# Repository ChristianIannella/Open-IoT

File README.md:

# Open IoT

Open IoT è un progetto open-source e open-hardware che ha lo scopo di offrire soluzioni IoT ai Maker e non solo.
Tutti i dispositivi Open IoT sono pronti per essere collegati all' impianto domestico, [qui](https://github.com/ChristianIannella/Open-IoT/tree/main) potete trovare schemi, gerber file ed esempi.

I dispositivi sono basati su ESP8266 e ESP32 questo permette connettività WiFi e [ESPNOW](https://www.espressif.com/en/solutions/low-power-solutions/esp-now), un protocollo proprietario ESPRESSIF. 

Le schede possono essere programmate sia da ambiente [Arduino](https://www.arduino.cc/en/software) sia [PlatformIO](https://platformio.org/) 

Su ogni dispositivo è presente un connettore FFC a 6 poli grazie al quale è possibile collegare il [programmatore](https://github.com/ChristianIannella/Open-IoT/tree/main/ESP%20Uploader) per cambiare firmware o testare il dispositivo.

# ELENCO DISPOSITIVI

- [ESP Uploader](https://github.com/ChristianIannella/Open-IoT/tree/main/ESP%20Uploader)
- [ESP8266 Relay](https://github.com/ChristianIannella/Open-IoT/tree/main/Relay)
- [ESP8266 Encoder](https://github.com/ChristianIannella/Open-IoT/tree/main/Encoder)
- [ESP8266 Thermometer](https://github.com/ChristianIannella/Open-IoT/tree/main/Thermometer)
- [ESP8266 Led Driver](https://github.com/ChristianIannella/Open-IoT/tree/main/LED%20Driver)
- [Smart Lamp](https://github.com/ChristianIannella/Open-IoT/tree/main/Smart%20Lamp)
- More coming soon.

## ISTRUZIONI MODULI ESP32

  - Arduino IDE
    
    Vai a `File`  `Impostazioni`  `URL Aggiuntive`
    
    Aggiungere il seguente URL: https://raw.githubusercontent.com/espressif/arduino-esp32/gh-pages/package_esp32_index.json

    Poi vai a `Strumenti`  `Scheda`  `Gestore Schede`

    Cerca esp32 e installa 

    In fine seleziona la seguente scheda `Adafruit ESP32 Feather`

    Ora puoi caricare il tuo sketch!

  - VS Code (PlatformIO):

    Avvia VS Code e vai a PIO Home `New project`

    Seleziona Board: `Adafruit ESP32 Feather` Framework: `Arduino`

    Il tuo file platformio.ini dovrà essere simile a questo:
    
      [env:featheresp32]
    
      platform = espressif32
  
      board = featheresp32
  
      framework = arduino 

## ISTRUZIONI MODULI ESP8266

  - Arduino IDE
    
    Vai a `File`  `Impostazioni`  `URL Aggiuntive`
    
    Aggiungere il seguente URL: https://arduino.esp8266.com/stable/package_esp8266com_index.json

    Poi vai a `Strumenti`  `Scheda`  `Gestore Schede`

    Cerca esp8266 e installa 

    In fine seleziona la seguente scheda `Generic ESP8266 Module`

    Ora puoi caricare il tuo sketch!

  - VS Code (PlatformIO):

    Avvia VS Code e vai a PIO Home `New project`

    Seleziona Board: `Adafruit HUZZAH ESP8266` Framework: `Arduino`

    Il tuo file platformio.ini dovrà essere simile a questo:
    
      [env:huzzah]
      
      platform = espressif8266
  
      board = huzzah
  
      framework = arduino

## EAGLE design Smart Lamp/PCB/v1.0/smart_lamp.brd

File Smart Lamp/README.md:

# Smart Lamp

Smart Lamp è basato su un ESP32 WROOM, a bordo è alloggiato un connettore USB-C e un CP2104 con circuito di auto-reset per il flash del MCU.
Oltre a quanto detto è anche presente un encoder e una porta per strip Led (NeoPixel, WS2812, etc.)
E' disponibile anche un' App tramite la quale è possibile pilotare uno o piu` dispositivi.
Questo sistema sfrutta il protocollo MQTT ma per ora senza certificati quindi assicurati di non appoggiarti a reti pubbliche e non usare password
che usi altrove o comuni!

Potrai usare qualsiasi broker mqtt come (broker.hivemq.com oppure broker.emqx.io) ricorda solo che dovrà essere lo stesso per tutti i dispositivi.

# User Guide

* [Come funziona l'App?](https://github.com/ChristianIannella/Open-IoT/tree/main/Smart%20Lamp/LampApp/App)

* [Come funziona il dispositivo?](https://github.com/ChristianIannella/Open-IoT/tree/main/Smart%20Lamp/LampApp/Firmware)

# Download

* [Android](https://play.google.com/store/apps/details?id=com.lampapp.lampapp&hl=it&gl=IT) 

* iOS: coming soon

# Contribute
Please, feel free to contribute.

# Author
Iannella Christian

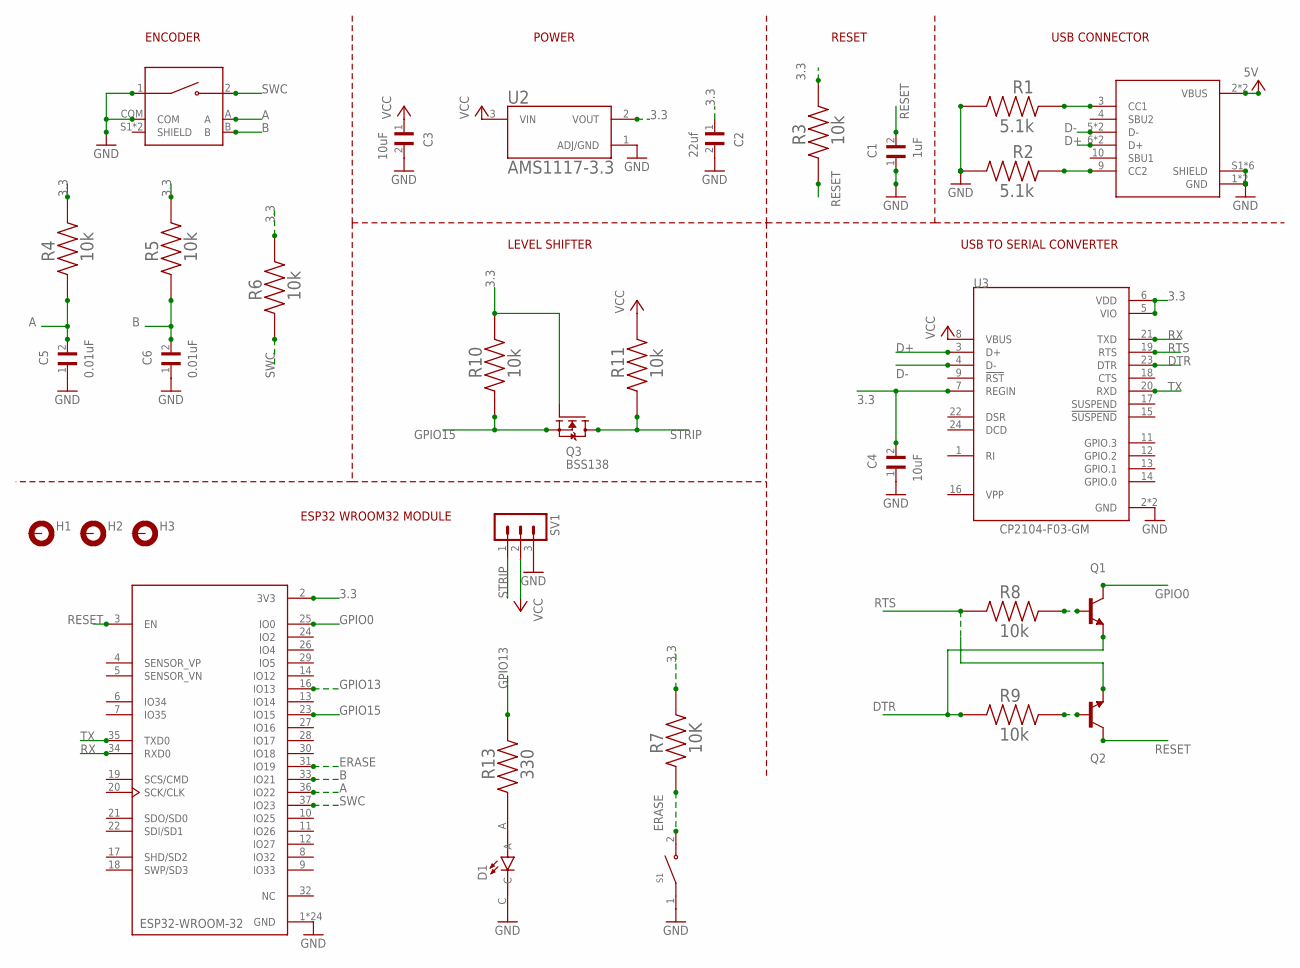
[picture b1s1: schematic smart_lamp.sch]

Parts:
C1: 1uF; CAPC2012X94N
C2: 22uf; CAPC2012X94N
C3, C4: 10uF; CAPC2012X94N
C5, C6: 0.01uF; CAPC2012X94N
D1: SML-LXT0805IW-TR; LEDC2012X120N
H1, H2, H3: MOUNT-PAD-ROUND3.2; 3,2-PAD
J1: DX07S016JA1R1500; JAE_DX07S016JA1R1500
MT1: PEC11R-4215F-S0024; XDCR_PEC11R-4215F-S0024
Q1, Q2: MMBT2222; SOT23-BEC
Q3: BSS138; SOT95P240X111-3N
R1, R2: 5.1k; RESC2012X60N
R3, R4, R5, R6, R8, R9, R10, R11: 10k; RESC2012X60N
R7: 10K; RESC2012X60N
R13: 330; RESC2012X60N
S1: PTS636_SM43J_SMTR_LFS; SW_PTS636_SM43J_SMTR_LFS
SV1: MA03-1
U1: ESP32-WROOM-32; MODULE_ESP32-WROOM-32
U2: AMS1117-3.3; SOT229P700X180-4N
U3: CP2104-F03-GM; QFN50P400X400X80-25N

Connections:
3.3: C2.1, C4.2, Q3.1 (G), R3.2, R4.2, R5.2, R6.2, R7.2, R10.2, U1.2 (3V3), U2.2 (VOUT), U3.5 (VIO), U3.6 (VDD), U3.7 (REGIN)
A: C5.2, MT1.A, R4.1, U1.36 (IO22)
B: C6.2, MT1.B, R5.1, U1.33 (IO21)
D+: J1.6 (D+), J1.7 (D+), U3.3 (D+)
D-: J1.5 (D-), J1.8 (D-), U3.4 (D-)
DTR: Q1.E, R9.1, U3.23 (DTR)
ERASE: R7.1, S1.2 (NO), U1.31 (IO19)
GND: C1.1, C2.2, C3.2, C4.1, C5.1, C6.1, D1.C, J1.1 (GND), J1.12 (GND), J1.S1 (SHIELD), J1.S2 (SHIELD), J1.S3 (SHIELD), J1.S4 (SHIELD), J1.S5 (SHIELD), J1.S6 (SHIELD), MT1.1, MT1.COM, R1.1, R2.1, S1.1 (COM), SV1.3, U1.1 (GND), U1.15 (GND), U1.38 (GND), U1.39_1 (GND), U1.39_2 (GND), U1.39_3 (GND), U1.39_4 (GND), U1.39_5 (GND), U1.39_6 (GND), U1.39_7 (GND), U1.39_8 (GND), U1.39_9 (GND), U1.39_10 (GND), U1.39_11 (GND), U1.39_12 (GND), U1.39_13 (GND), U1.39_14 (GND), U1.39_15 (GND), U1.39_16 (GND), U1.39_17 (GND), U1.39_18 (GND), U1.39_19 (GND), U1.39_20 (GND), U1.39_21 (GND), U2.1 (ADJ/GND), U3.2 (GND), U3.25 (GND)
GPIO0: Q1.C, U1.25 (IO0)
GPIO13: R13.2, U1.16 (IO13)
GPIO15: Q3.2 (S), R10.1, U1.23 (IO15)
unnamed: J1.3 (CC1), R1.2
unnamed: J1.9 (CC2), R2.2
unnamed: Q1.B, R8.2
unnamed: Q2.B, R9.2
unnamed: D1.A, R13.1
RESET: C1.2, Q2.C, R3.1, U1.3 (EN)
RTS: Q2.E, R8.1, U3.19 (RTS)
RX: U1.34 (RXD0), U3.21 (TXD)
STRIP: Q3.3 (D), R11.1, SV1.1
SWC: MT1.2, R6.1, U1.37 (IO23)
TX: U1.35 (TXD0), U3.20 (RXD)
VCC: C3.1, J1.2 (VBUS), J1.11 (VBUS), R11.2, SV1.2, U2.3 (VIN), U3.8 (VBUS)

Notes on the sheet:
USB CONNECTOR
RESET
POWER
ENCODER
USB TO SERIAL CONVERTER
LEVEL SHIFTER
ESP32 WROOM32 MODULE

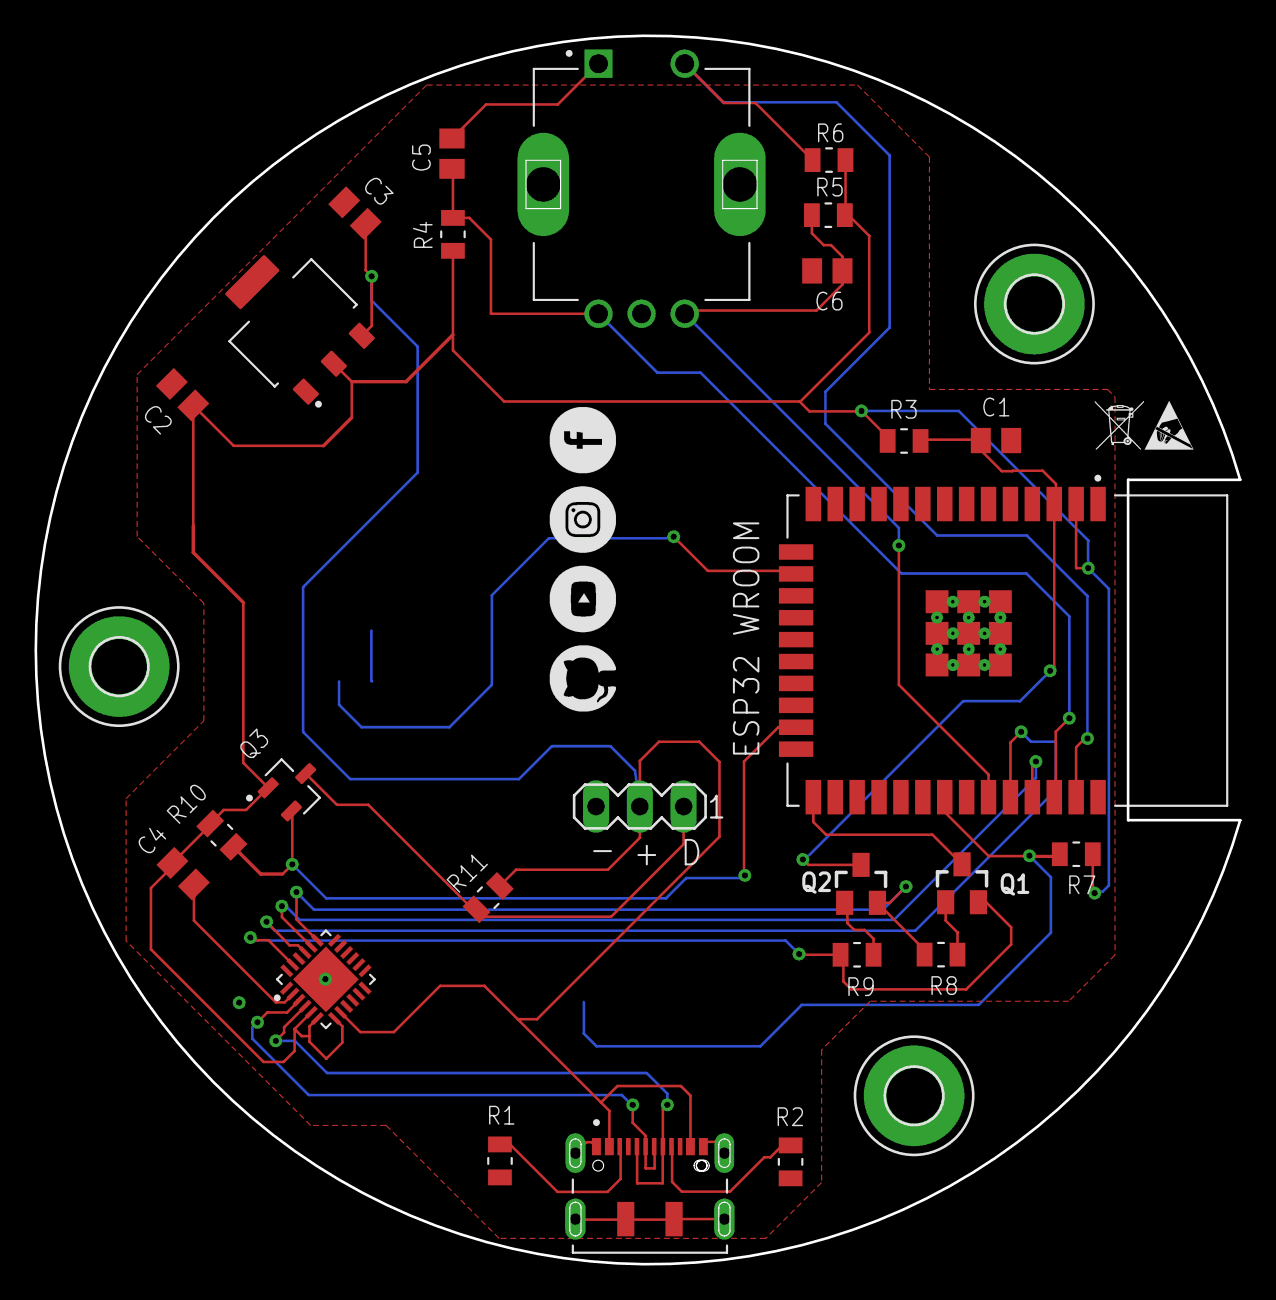
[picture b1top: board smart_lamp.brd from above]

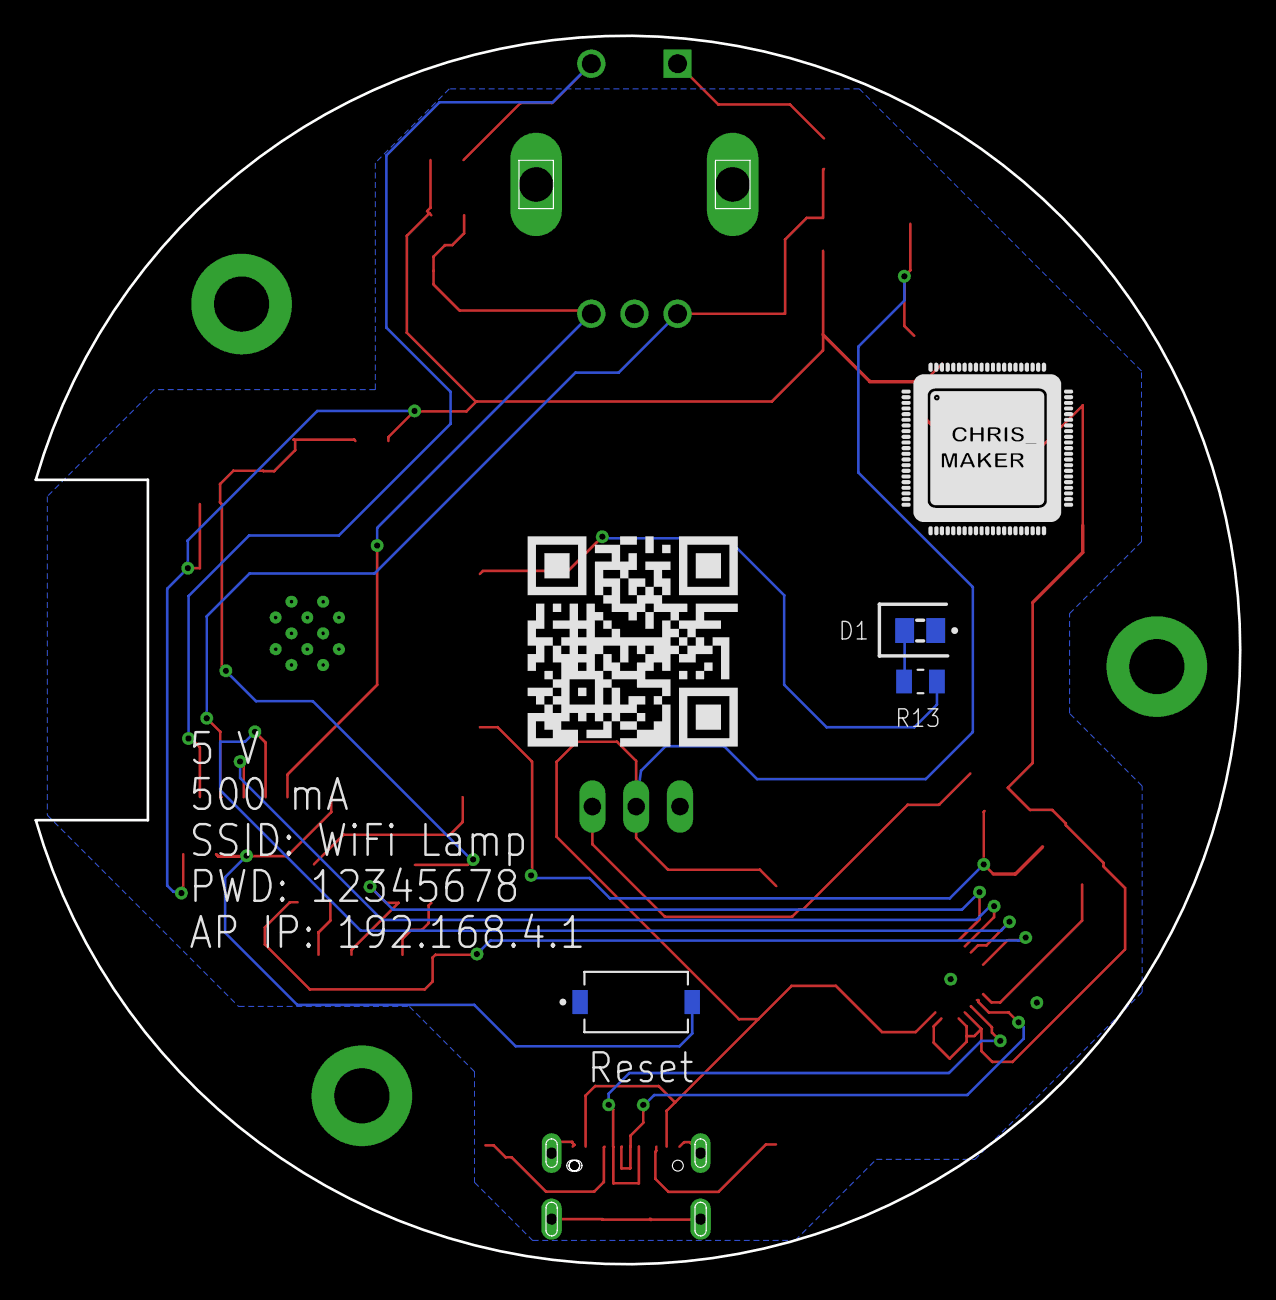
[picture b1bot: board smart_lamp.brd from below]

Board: 2 copper layers, 69.8 x 71.2 mm, 32 parts (3 on the bottom side), 23 nets.

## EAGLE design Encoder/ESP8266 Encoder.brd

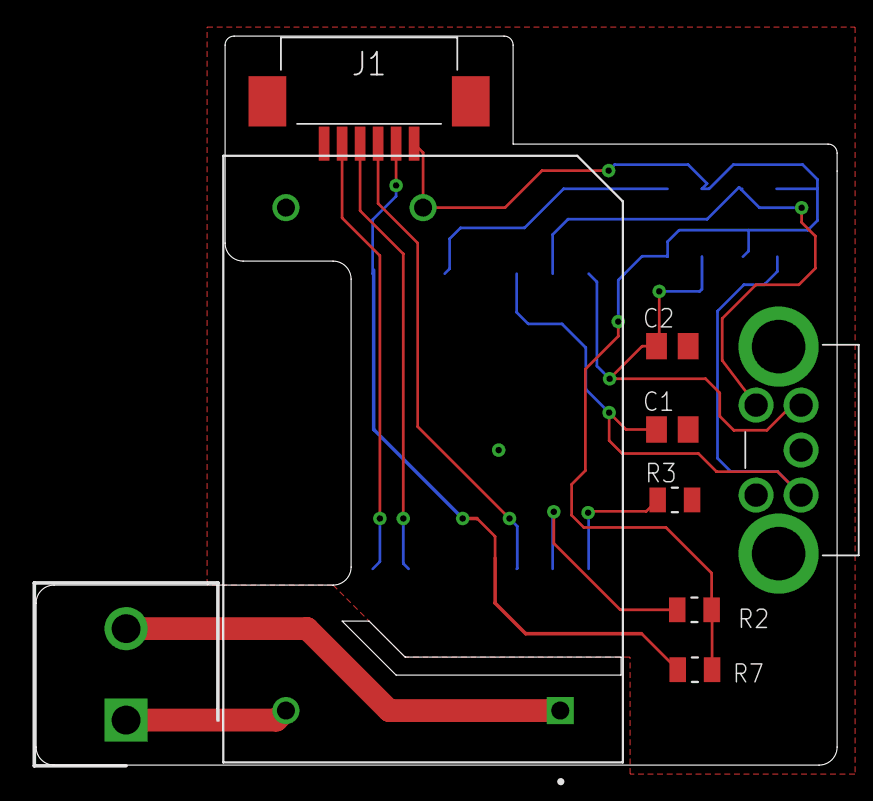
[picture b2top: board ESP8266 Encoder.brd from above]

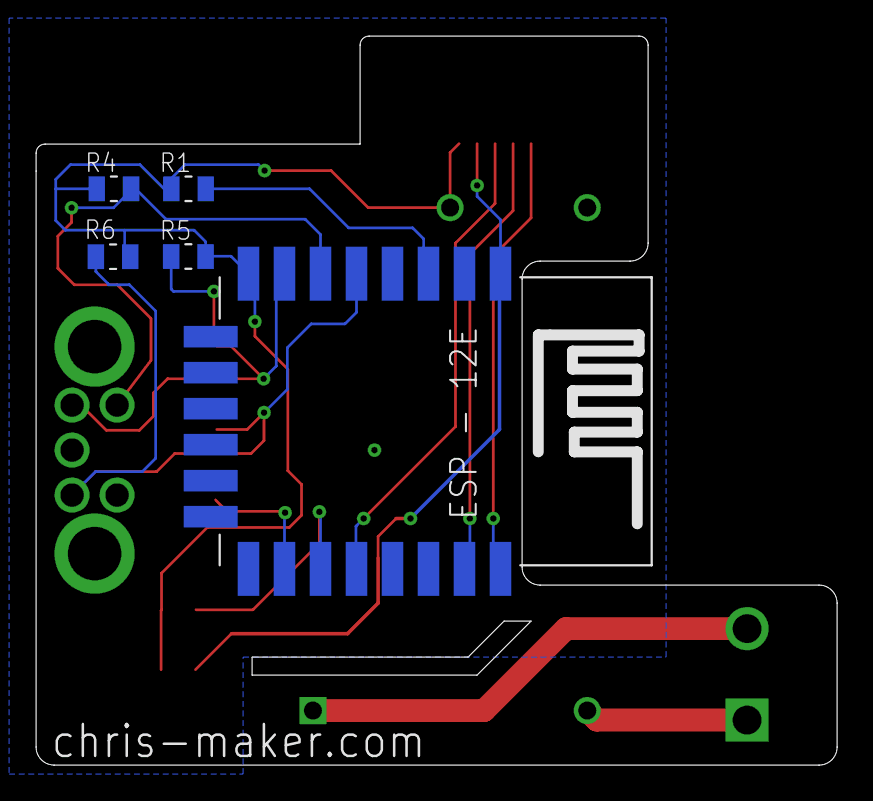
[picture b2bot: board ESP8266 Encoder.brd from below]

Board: 2 copper layers, 44.5 x 40.5 mm, 14 parts (5 on the bottom side), 14 nets.

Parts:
C1, C2: 0.1uF; CAPC2012X94N
J1: 52852-0670; 528520670
J3: TB004-508-02BE; SHDR2W100P0X508_1X2_1016X1020X
PS2: RAC02-3.3SGB; CONV_RAC02-3.3SGB
R1, R2, R4, R5, R6, R7: 10K; RESC2012X60N
R3: 4.7K; RESC2012X60N
U1: ENCODER90; EN11VSM0AF20
U2: ESP12E-SMD

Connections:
CH_PD: R1.1, U2.CH_PD
GND: C1.2, C2.2, J1.6, PS2.3, R3.1, U1.3, U1.4, U2.GND
GPIO0: J1.3, U2.GPIO0
GPIO2: R2.1, U2.GPIO2
GPIO12: R4.1, U1.5, U2.GPIO12
GPIO13: C2.1, R5.1, U1.2, U2.GPIO13
GPIO14: C1.1, R6.1, U1.1, U2.GPIO14
GPIO15: R3.2, U2.GPIO15
unnamed: J3.2, PS2.1
unnamed: J3.1, PS2.2
RESET: J1.2, R7.1, U2.RESET
RX: J1.5, U2.TXD0
TX: J1.4, U2.RXD0
VCC: J1.1, PS2.4, R1.2, R2.2, R4.2, R5.2, R6.2, R7.2, U2.VCC

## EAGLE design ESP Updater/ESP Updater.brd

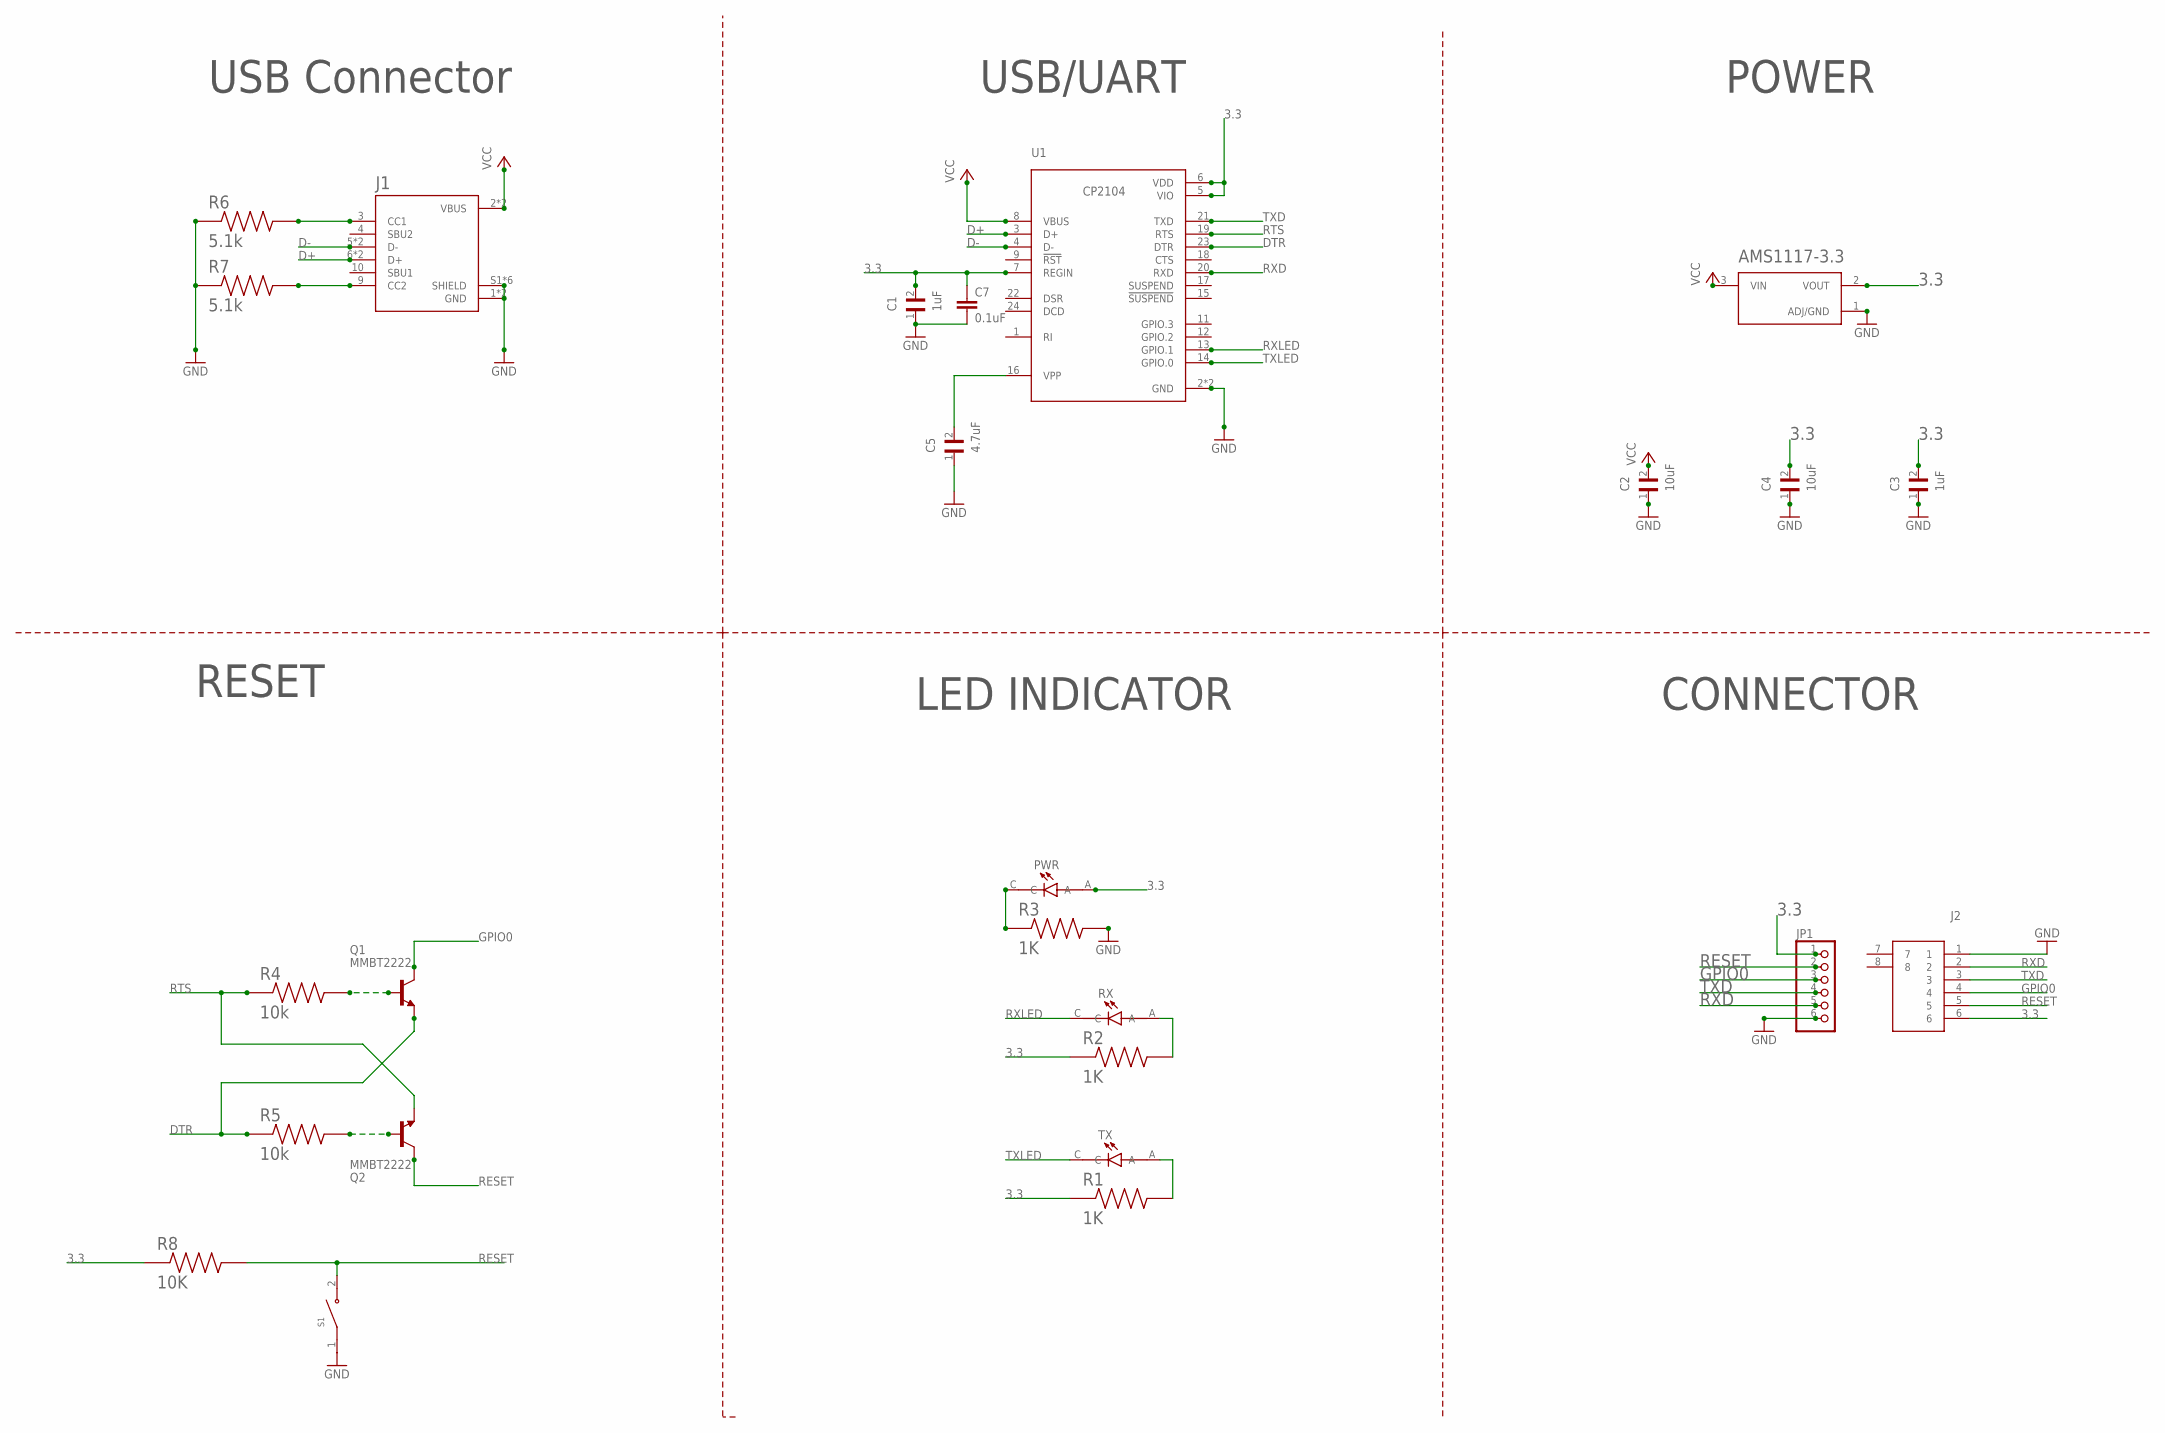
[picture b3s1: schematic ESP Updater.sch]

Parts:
C1, C3: 1uF; CAPC2012X94N
C2, C4: 10uF; CAPC2012X94N
C5: 4.7uF; CAPC2012X94N
C7: 0.1uF; C0603
J1: DX07S016JA1R1500; JAE_DX07S016JA1R1500
J2: 52852-0670; 528520670
JP1: PINHD-1X6; 1X06
PWR: SML-LXT0805IW-TR; LEDC2012X120N
Q1, Q2: MMBT2222; SOT23-BEC
R1, R2, R3: 1K; RESC2012X60N
R4, R5: 10k; RESC2012X60N
R6, R7: 5.1k; RESC2012X60N
R8: 10K; RESC2012X60N
RX: SML-LXT0805IW-TR; LEDC2012X120N
S1: PTS636_SM43J_SMTR_LFS; SW_PTS636_SM43J_SMTR_LFS
TX: SML-LXT0805IW-TR; LEDC2012X120N
U1: CP2104; QFN50P400X400X80-25N
U2: AMS1117-3.3; SOT229P700X180-4N

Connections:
3.3: C1.2, C3.2, C4.2, C7.1, J2.6, JP1.1, PWR.A, R1.1, R2.1, R8.1, U1.5 (VIO), U1.6 (VDD), U1.7 (REGIN), U2.2 (VOUT)
D+: J1.6 (D+), J1.7 (D+), U1.3 (D+)
D-: J1.5 (D-), J1.8 (D-), U1.4 (D-)
DTR: Q1.E, R5.1, U1.23 (DTR)
GND: C1.1, C2.1, C3.1, C4.1, C5.1, C7.2, J1.1 (GND), J1.12 (GND), J1.S1 (SHIELD), J1.S2 (SHIELD), J1.S3 (SHIELD), J1.S4 (SHIELD), J1.S5 (SHIELD), J1.S6 (SHIELD), J2.1, JP1.6, R3.2, R6.1, R7.1, S1.1 (COM), U1.2 (GND), U1.25 (GND), U2.1 (ADJ/GND)
GPIO0: J2.4, JP1.3, Q1.C
unnamed: J1.3 (CC1), R6.2
unnamed: J1.9 (CC2), R7.2
unnamed: PWR.C, R3.1
unnamed: R2.2, RX.A
unnamed: R1.2, TX.A
unnamed: Q2.B, R5.2
unnamed: Q1.B, R4.2
unnamed: C5.2, U1.16 (VPP)
RESET: J2.5, JP1.2, Q2.C, R8.2, S1.2 (NO)
RTS: Q2.E, R4.1, U1.19 (RTS)
RXD: J2.2, JP1.5, U1.20 (RXD)
RXLED: RX.C, U1.13 (GPIO.1)
TXD: J2.3, JP1.4, U1.21 (TXD)
TXLED: TX.C, U1.14 (GPIO.0)
VCC: C2.2, J1.2 (VBUS), J1.11 (VBUS), U1.8 (VBUS), U2.3 (VIN)

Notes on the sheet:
USB Connector
USB/UART
POWER
CONNECTOR
RESET
LED INDICATOR

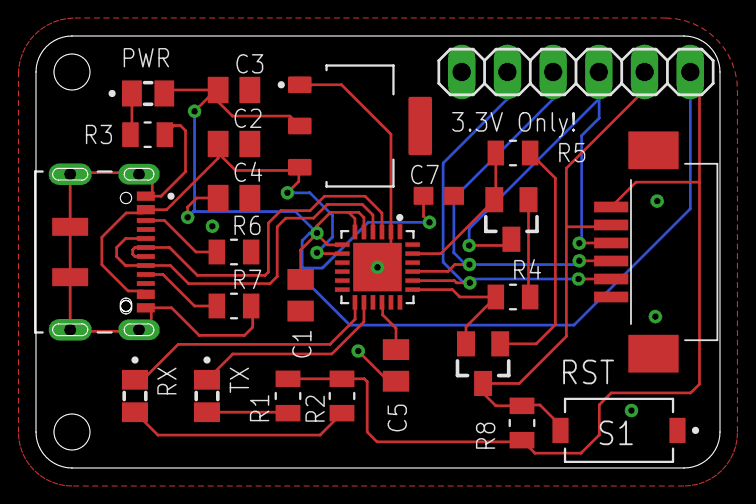
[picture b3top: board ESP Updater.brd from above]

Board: 2 copper layers, 38.0 x 24.0 mm, 25 parts (0 on the bottom side), 21 nets.

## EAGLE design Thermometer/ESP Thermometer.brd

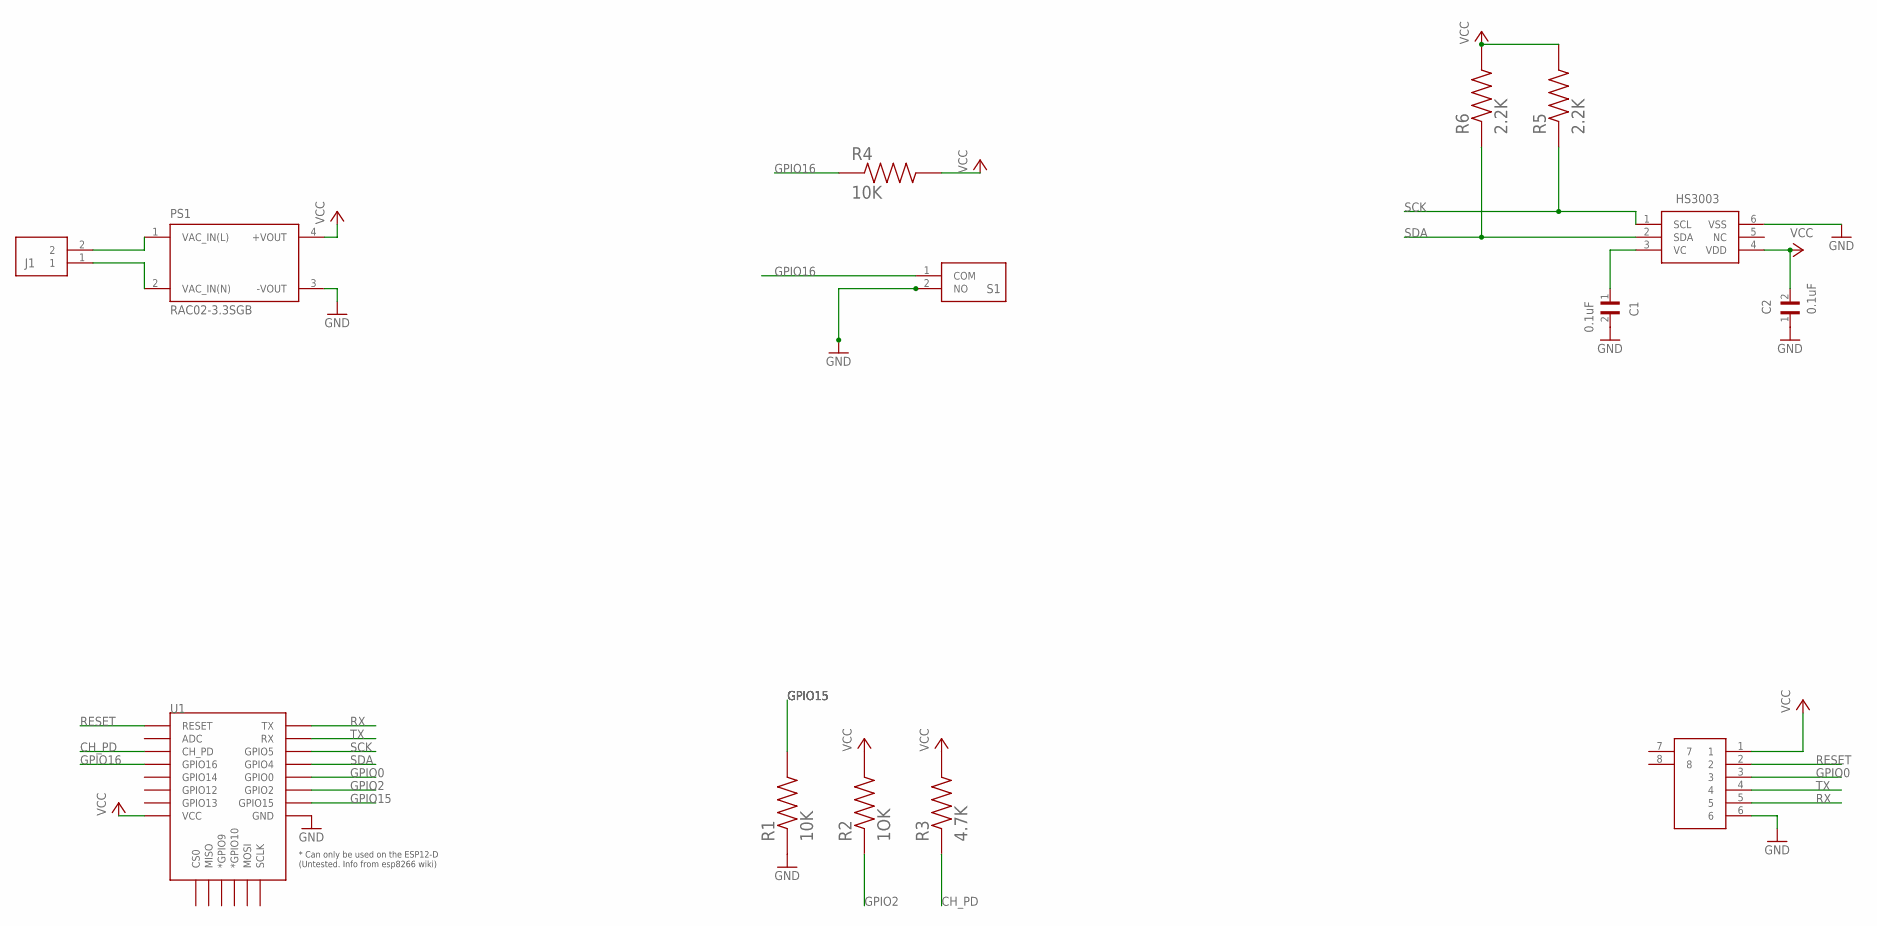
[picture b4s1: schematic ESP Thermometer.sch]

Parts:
C1, C2: 0.1uF; CAPC2012X94N
IC1: HS3003; HS3004
J1: TB006-508-02BE; TB00650802BE
J2: 52852-0670; 528520670
PS1: RAC02-3.3SGB; CONV_RAC02-3.3SGB
R1, R4: 10K; RESC2012X60N
R2: 1OK; RESC2012X60N
R3: 4.7K; RESC2012X60N
R5, R6: 2.2K; RESC2012X60N
S1: PTS636_SP50_SMTR_LFS; PTS636SP50SMTRLFS
U1: ESP12ESMD; ESP12E-SMD

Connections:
CH_PD: R3.1, U1.CH_PD
GND: C1.2, C2.1, IC1.6 (VSS), J2.6, PS1.3 (-VOUT), R1.1, S1.2 (NO), U1.GND
GPIO0: J2.3, U1.GPIO0
GPIO2: R2.1, U1.GPIO2
GPIO15: R1.2, U1.GPIO15
GPIO16: R4.1, S1.1 (COM), U1.GPIO16
unnamed: J1.2, PS1.1 (VAC_IN(L))
unnamed: J1.1, PS1.2 (VAC_IN(N))
unnamed: C1.1, IC1.3 (VC)
RESET: J2.2, U1.RESET
RX: J2.5, U1.TXD0 (TX)
SCK: IC1.1 (SCL), R5.1, U1.GPIO5
SDA: IC1.2 (SDA), R6.1, U1.GPIO4
TX: J2.4, U1.RXD0 (RX)
VCC: C2.2, IC1.4 (VDD), J2.1, PS1.4 (+VOUT), R2.2, R3.2, R4.2, R5.2, R6.2, U1.VCC

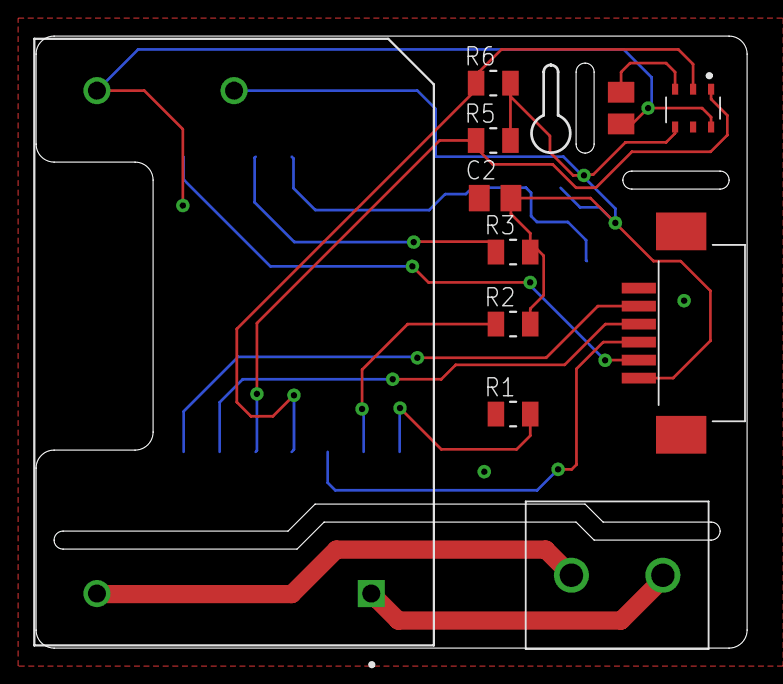
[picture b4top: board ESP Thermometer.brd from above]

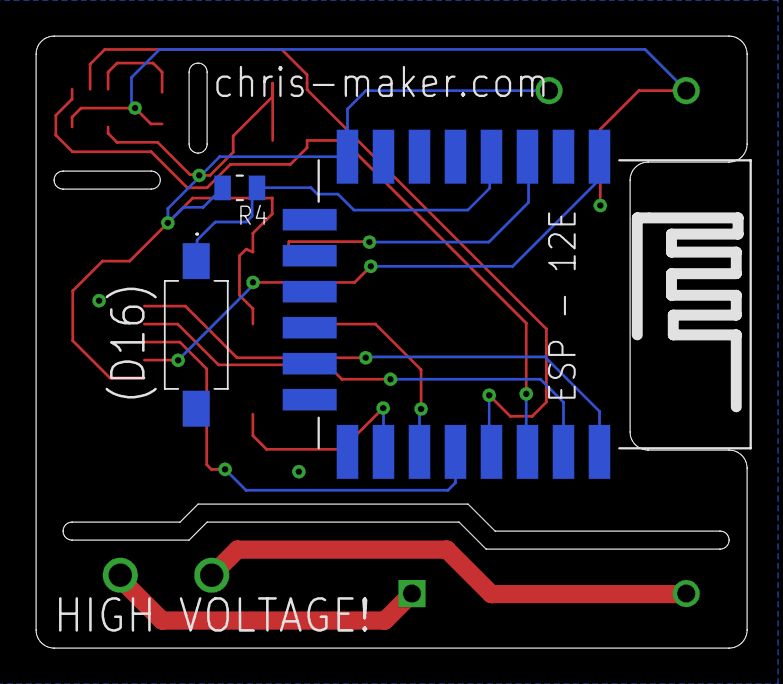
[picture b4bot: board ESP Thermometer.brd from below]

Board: 2 copper layers, 39.5 x 34.0 mm, 14 parts (3 on the bottom side), 15 nets.

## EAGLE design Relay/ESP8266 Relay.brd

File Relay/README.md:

# ESP8266 Relay

# SPECIFICHE TECNICHE

- Alimentazione 220VAC
- Relè stato solido 220VAC 2A
- Fusibile sostituibile 2A
- MCU ESP8266
- WiFi
- 1 GPIO (D14)

| PINOUT |  |
|---|---|
|Service Button|D12 (10K external pull-up)|
|Switch Button|D14 (10K external pull-up)|
|Switch Led|D13 (10K external pull-up)|

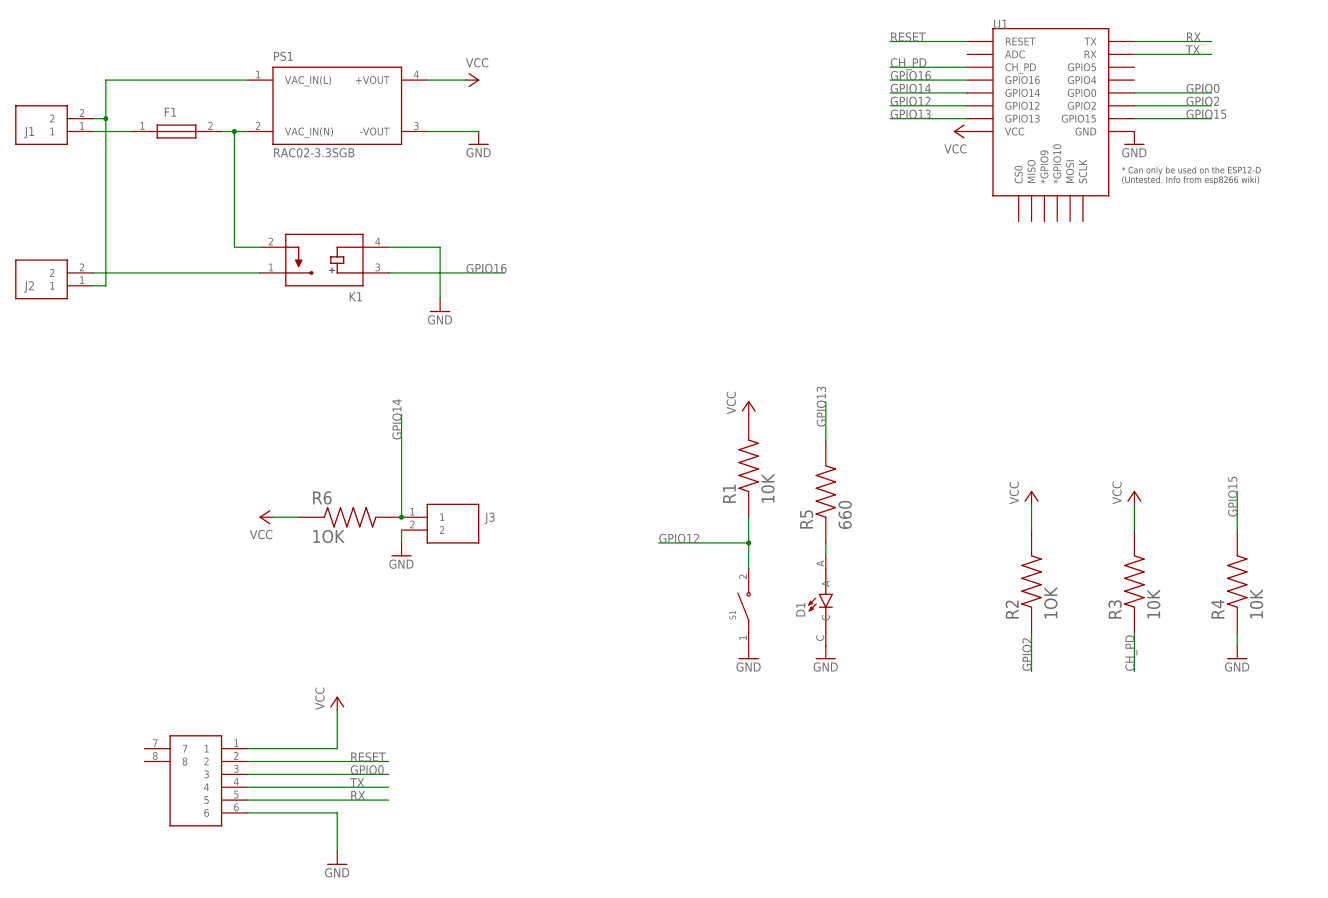
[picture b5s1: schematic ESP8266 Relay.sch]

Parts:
D1: SML-LXT0805IW-TR; LEDC2012X120N
F1: 3404.2469.22; 3404246922
J1, J2, J3: TB006-508-02BE; TB00650802BE
J4: 52852-0670; 528520670
K1: G3MB-202PDC5; RELAY_G3MB-202PDC5
PS1: RAC02-3.3SGB; CONV_RAC02-3.3SGB
R1, R3, R4: 10K; RESC2012X60N
R2, R6: 1OK; RESC2012X60N
R5: 660; RESC2012X60N
S1: PTS636_SM43J_SMTR_LFS; SW_PTS636_SM43J_SMTR_LFS
U1: ESP12ESMD; ESP12E-SMD

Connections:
CH_PD: R3.1, U1.CH_PD
GND: D1.C, J3.2, J4.6, K1.4, PS1.3 (-VOUT), R4.1, S1.1 (COM), U1.GND
GPIO0: J4.3, U1.GPIO0
GPIO2: R2.1, U1.GPIO2
GPIO12: R1.1, S1.2 (NO), U1.GPIO12
GPIO13: R5.2, U1.GPIO13
GPIO14: J3.1, R6.2, U1.GPIO14
GPIO15: R4.2, U1.GPIO15
GPIO16: K1.3, U1.GPIO16
unnamed: F1.2, K1.2, PS1.2 (VAC_IN(N))
unnamed: F1.1, J1.1
unnamed: J1.2, J2.1, PS1.1 (VAC_IN(L))
unnamed: J2.2, K1.1
unnamed: D1.A, R5.1
RESET: J4.2, U1.RESET
RX: J4.5, U1.TXD0 (TX)
TX: J4.4, U1.RXD0 (RX)
VCC: J4.1, PS1.4 (+VOUT), R1.2, R2.2, R3.2, R6.1, U1.VCC

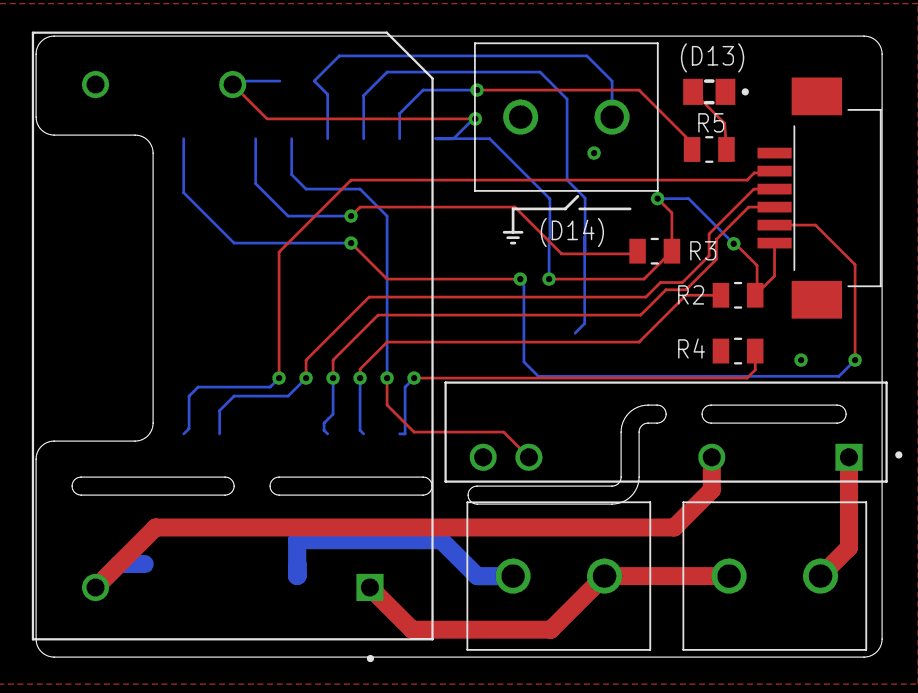
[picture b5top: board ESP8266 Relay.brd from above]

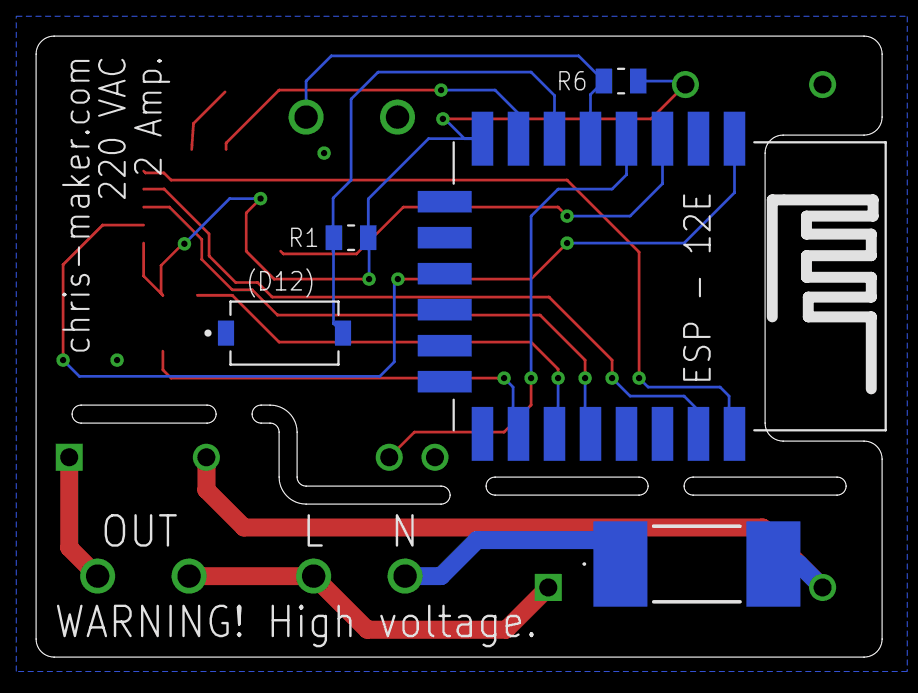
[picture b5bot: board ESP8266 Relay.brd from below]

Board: 2 copper layers, 47.0 x 34.5 mm, 16 parts (5 on the bottom side), 18 nets.

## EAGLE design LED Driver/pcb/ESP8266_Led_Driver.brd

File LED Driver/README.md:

# ESP8266 Led Driver

# SPECIFICHE TECNICHE

- Alimentazione 5VDC
- MCU ESP8266
- WiFi
- 1 GPIO (D13)

| PINOUT |  |
|---|---|
|Service Button|D12 (10K external pull-up)|
|Strip Led Output|D13|

|FFC||
|---|---|
|1|3.3V|
|2|RESET|
|3|GPIO0|
|4|TX|
|5|RX|
|6|GND|

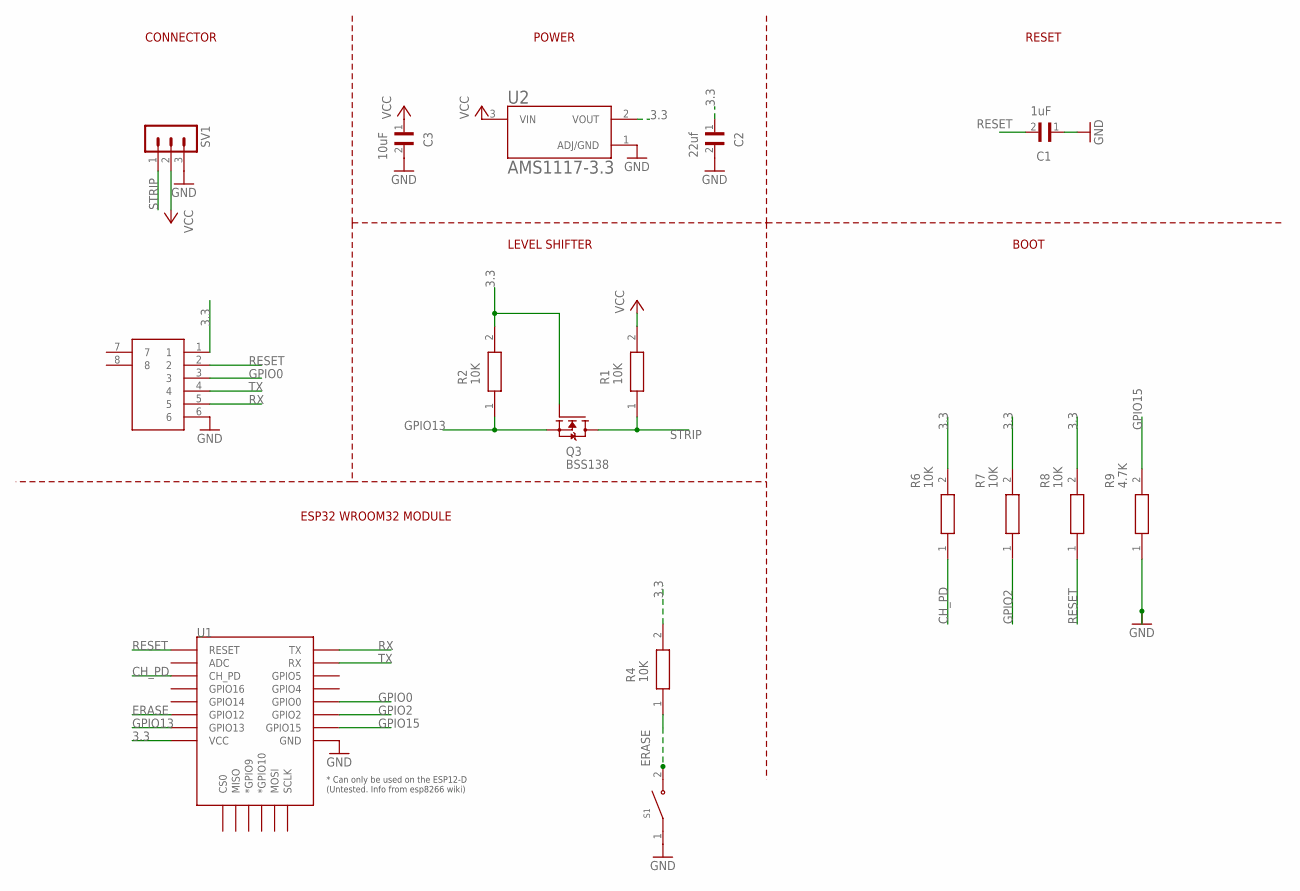
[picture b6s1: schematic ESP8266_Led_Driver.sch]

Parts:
C1: 1uF; CAPC2012X94N
C2: 22uf; CAPC2012X94N
C3: 10uF; CAPC2012X94N
J1: 52852-0670; 528520670
Q3: BSS138; SOT95P240X111-3N
R1, R2, R4, R6, R7, R8: 10K; RESC1608X55N
R9: 4.7K; RESC1608X55N
S1: PTS636_SM43J_SMTR_LFS; SW_PTS636_SM43J_SMTR_LFS
SV1: MA03-1
U1: ESP12ESMD; ESP12E-SMD
U2: AMS1117-3.3; SOT229P700X180-4N

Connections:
3.3: C2.1, J1.1, Q3.1 (G), R2.2, R4.2, R6.2, R7.2, R8.2, U1.VCC, U2.2 (VOUT)
CH_PD: R6.1, U1.CH_PD
ERASE: R4.1, S1.2 (NO), U1.GPIO12
GND: C1.1, C2.2, C3.2, J1.6, R9.1, S1.1 (COM), SV1.3, U1.GND, U2.1 (ADJ/GND)
GPIO0: J1.3, U1.GPIO0
GPIO2: R7.1, U1.GPIO2
GPIO13: Q3.2 (S), R2.1, U1.GPIO13
GPIO15: R9.2, U1.GPIO15
RESET: C1.2, J1.2, R8.1, U1.RESET
RX: J1.5, U1.TXD0 (TX)
STRIP: Q3.3 (D), R1.1, SV1.1
TX: J1.4, U1.RXD0 (RX)
VCC: C3.1, R1.2, SV1.2, U2.3 (VIN)

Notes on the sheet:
RESET
POWER
LEVEL SHIFTER
ESP32 WROOM32 MODULE
CONNECTOR
BOOT

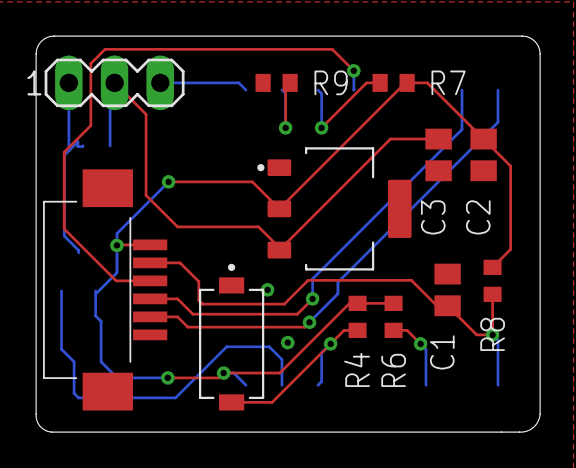
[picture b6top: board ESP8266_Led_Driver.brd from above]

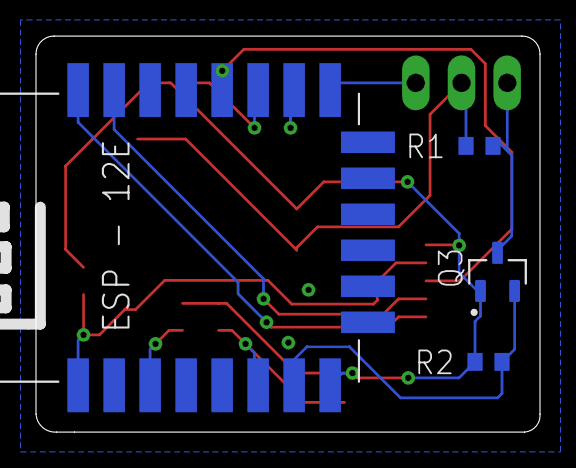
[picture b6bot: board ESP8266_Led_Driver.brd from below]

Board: 2 copper layers, 28.0 x 22.0 mm, 16 parts (4 on the bottom side), 13 nets.

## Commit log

2023-10-09 Upload
2023-10-09 Uploading
